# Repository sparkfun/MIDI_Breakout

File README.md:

SparkFun MIDI Breakout - MIDI In/Out/Thru For Microcontrollers
========================================

[
*MIDI Breakout (BOB-09598)*](https://cdn.sparkfun.com//assets/parts/3/4/1/6/09598-04.jpg)

The MIDI Breakout board gives your Arduino or any other microcontroller access to the MIDI communication protocol. The MIDI protocol shares many similarities with standard asynchronous serial interfaces, so you can use the UART pins of your microcontroller to send and receive MIDI’s event messages.

The MIDI Breakout provides both MIDI-IN and MIDI-OUT connections, as well as a MIDI-THRU port. The MIDI-IN port is opto-isolated to prevent ground loops. The MIDI Breakout board can be mounted directly on top of an Arduino like a shield, connecting the MIDI-IN/THRU to the Arduino’s hardware RX pin and the MIDI-OUT to TX. All of the Arduino’s digital and analog pins, as well as power and ground busses, are broken out as well. The RUN/PGM switch allows you to program the Arduino over serial without having to remove the shield.

Repository Contents
-------------------
* **/Hardware** - All Eagle design files (.brd, .sch, .STL)

Product Versions
----------------
* [BOB-09598](https://www.sparkfun.com/products/9598) - MIDI breakout board 

License Information
-------------------
The hardware is released under [Creative Commons ShareAlike 4.0 International](https://creativecommons.org/licenses/by-sa/4.0/).

Distributed as-is; no warranty is given.

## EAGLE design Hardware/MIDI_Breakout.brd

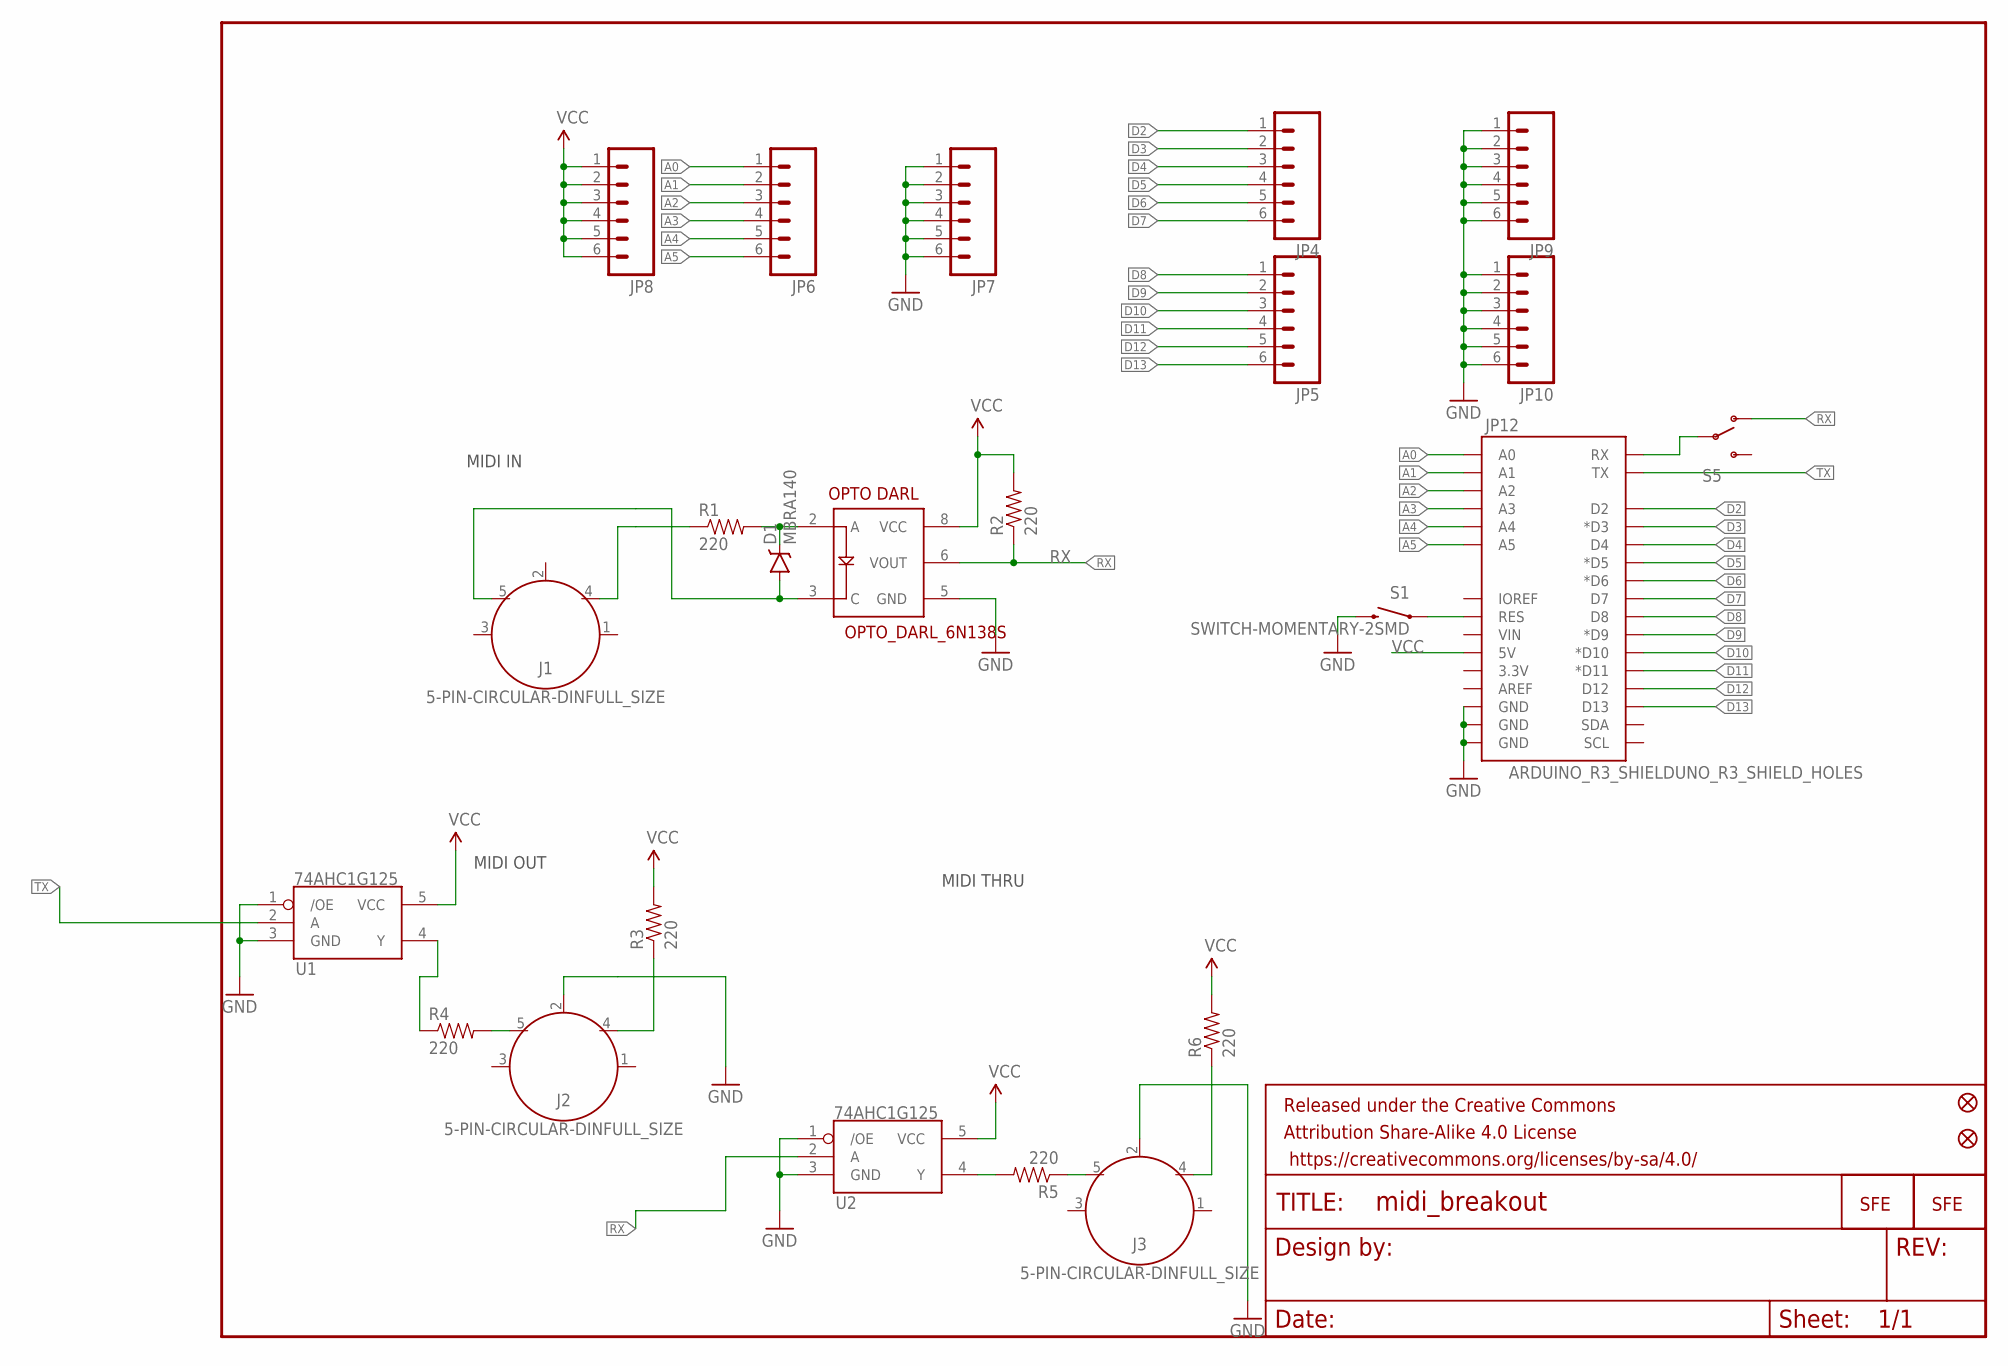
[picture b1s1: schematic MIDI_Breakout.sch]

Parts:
D1: MBRA140; SMA-DIODE
FID1, FID2: FIDUCIALUFIDUCIAL; MICRO-FIDUCIAL
FRAME1: frame; CREATIVE_COMMONS
J1, J2, J3: 5-PIN-CIRCULAR-DINFULL_SIZE; 5-PIN-DIN-RA-PCB
JP3, JP11: LOGO-SFENEW; SFE-NEW-WEBLOGO
JP4, JP5, JP6, JP7, JP8, JP9, JP10: M06SIP; 1X06
JP12: ARDUINO_R3_SHIELDUNO_R3_SHIELD_HOLES; UNO_R3_SHIELD_HOLES
R1, R2, R3, R4, R5, R6: 220; 0603-RES
S1: SWITCH-MOMENTARY-2SMD; TACTILE-SWITCH-SMD
S5: SWITCH-SPDTSMD; AYZ0202
U1, U2: 74AHC1G125; SOT23-5
U$6: OPTO_DARL_6N138S; 8-SMD

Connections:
56: D1.C, R1.2, U$6.2 (A)
1235: J2.4, R3.1
A0: JP6.1, JP12.A0
A1: JP6.2, JP12.A1
A2: JP6.3, JP12.A2
A3: JP6.4, JP12.A3
A4: JP6.5, JP12.A4
A5: JP6.6, JP12.A5
D2: JP4.1, JP12.D2
D3: JP4.2, JP12.D3 (*D3)
D4: JP4.3, JP12.D4
D5: JP4.4, JP12.D5 (*D5)
D6: JP4.5, JP12.D6 (*D6)
D7: JP4.6, JP12.D7
D8: JP5.1, JP12.D8
D9: JP5.2, JP12.D9 (*D9)
D10: JP5.3, JP12.D10 (*D10)
D11: JP5.4, JP12.D11 (*D11)
D12: JP5.5, JP12.D12
D13: JP5.6, JP12.D13
GND: J2.2, J3.2, JP7.1, JP7.2, JP7.3, JP7.4, JP7.5, JP7.6, JP9.1, JP9.2, JP9.3, JP9.4, JP9.5, JP9.6, JP10.1, JP10.2, JP10.3, JP10.4, JP10.5, JP10.6, JP12.GND@0 (GND), JP12.GND@1 (GND), JP12.GND@2 (GND), S1.3 (2), U1.1 (/OE), U1.3 (GND), U2.1 (/OE), U2.3 (GND), U$6.5 (GND)
unnamed: J3.5, R5.1
unnamed: R5.2, U2.4 (Y)
unnamed: J1.4, R1.1
unnamed: JP12.RX, S5.2
unnamed: JP12.RES, S1.1
unnamed: J2.5, R4.2
unnamed: J3.4, R6.1
unnamed: R4.1, U1.4 (Y)
PIN5: D1.A, J1.5, U$6.3 (C)
RX: R2.1, S5.1 (O), U2.2 (A), U$6.6 (VOUT)
TX: JP12.TX, U1.2 (A)
VCC: JP8.1, JP8.2, JP8.3, JP8.4, JP8.5, JP8.6, JP12.5V, R2.2, R3.2, R6.2, U1.5 (VCC), U2.5 (VCC), U$6.8 (VCC)

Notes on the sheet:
MIDI IN
MIDI OUT
MIDI THRU

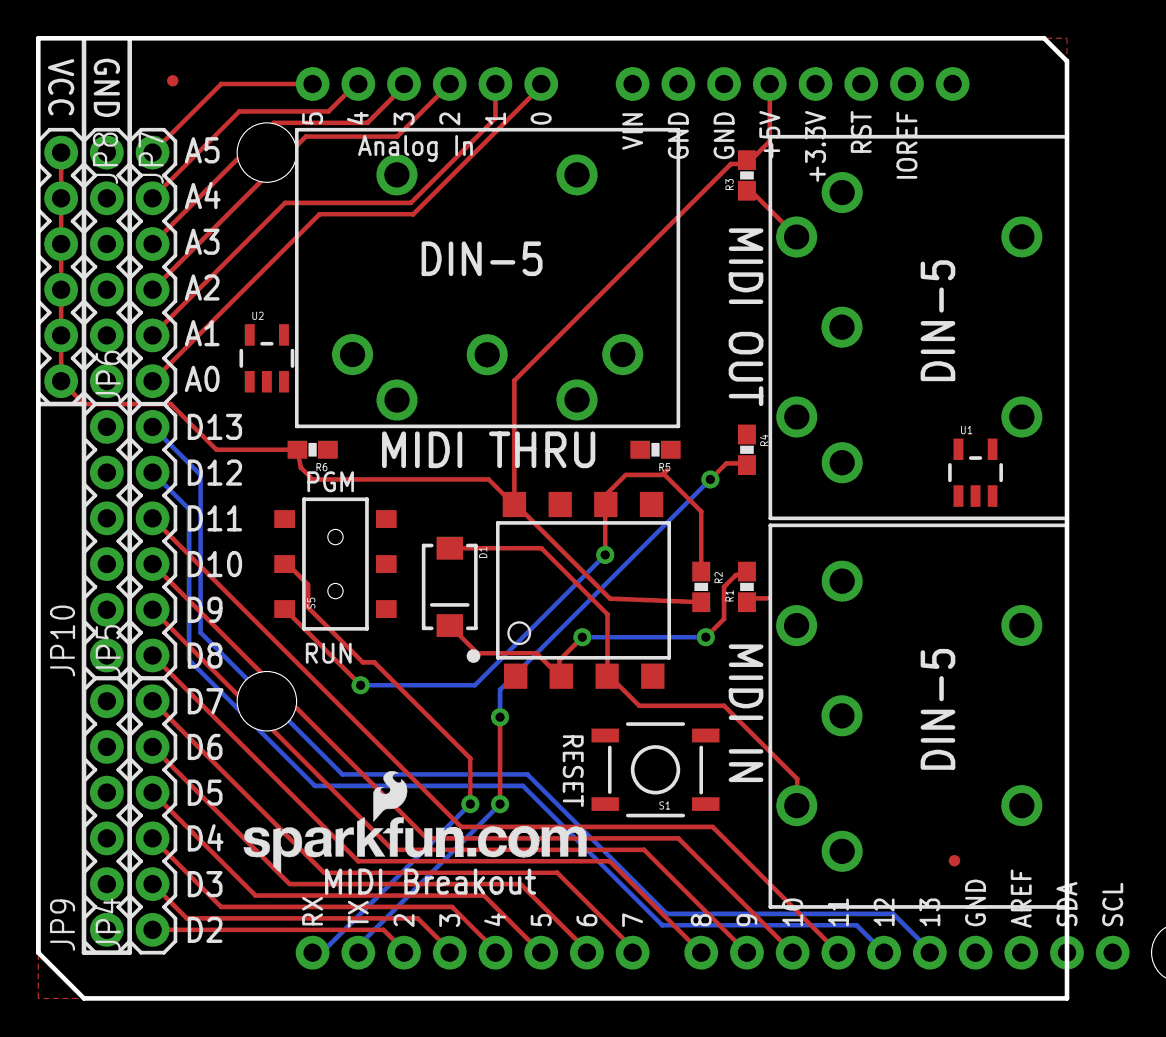
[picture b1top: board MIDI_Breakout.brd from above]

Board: 2 copper layers, 57.1 x 53.3 mm, 28 parts (1 on the bottom side), 33 nets.

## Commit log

2015-02-16 Initial Commit
    Starting repo with V11 PCB files.
2015-02-17 Changes WIP.
2015-05-06 Updating brd file with version number
